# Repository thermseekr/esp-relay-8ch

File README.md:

# ESP-RELAY-8CH

ESP32 based board with 8x 24 VDC inputs and 8x 10A relay outputs.

This board is designed to be controlled by an Olimex ESP32-POE or ESP32-POE-ISO modules.

The dimensions are such that the board can be mounted on a PCB DIN rail holder from the Brazilian manufacturer Metaltex, check [here](https://www.metaltex.com.br/produtos/componentes/suportes/sp7-suporte-para-montagem-de-placa-de-circuito-impresso-em-trilho-din) for details.

## LICENSE

This project is licensed under the [Creative Commons BY-NC 4.0 License](https://creativecommons.org/licenses/by-nc/4.0/).
Commercial use is not permitted without prior written consent. See the [LICENSE.txt](LICENSE.txt) file for details.

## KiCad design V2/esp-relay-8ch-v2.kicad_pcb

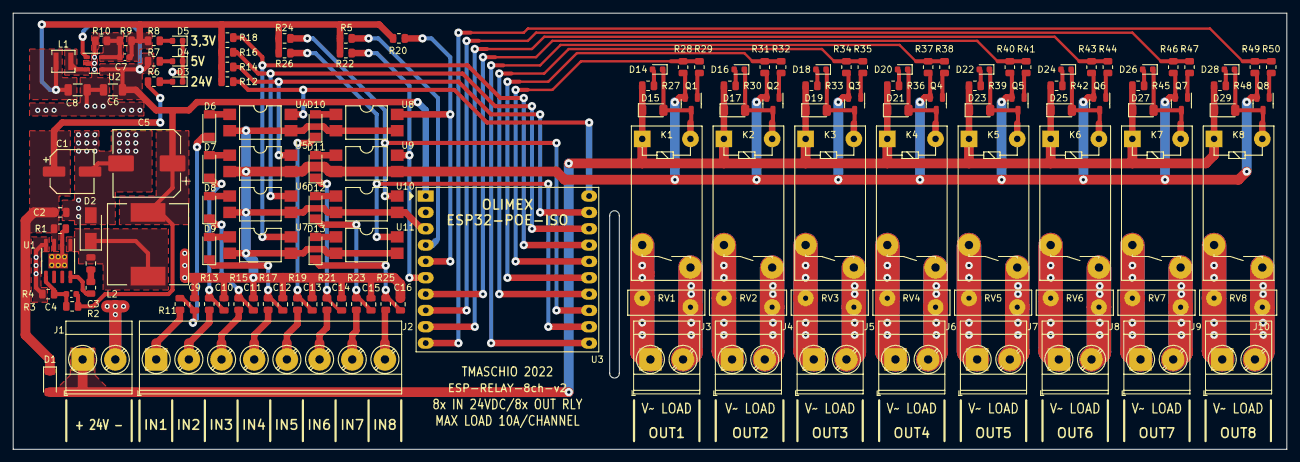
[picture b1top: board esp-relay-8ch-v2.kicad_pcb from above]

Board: 2 copper layers, 198.0 x 67.8 mm, 142 parts (0 on the bottom side), 96 nets.

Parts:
C1: 47uF/35V/6,3x5,4; CP_Elec_6.3x5.4
C2, C3: 0,1uF/50V/0805; C_0805_2012Metric
C4: 12pF/50V/0603; C_0603_1608Metric
C5: 470uF/16V/10x10; CP_Elec_10x10
C6, C8: 10uF/16V/1206; C_1206_3216Metric
C7: 22pF/50V/0603; C_0603_1608Metric
C9, C10, C11, C12, C13, C14, C15, C16: 33nF/50V/0805; C_0805_2012Metric
D1: SM4007PL/SOD-123; D_SOD-123
D2: SS510; D_SMA
D3, D4, D5, D14, D16, D18, D20, D22, D24, D26, D28: BLUE/0603; LED_0603_1608Metric
D6, D7, D8, D9, D10, D11, D12, D13: 9V1/500mW; D_MiniMELF
D15, D17, D19, D21, D23, D25, D27, D29: 1N4148/SOD-123; D_SOD-123
J1: +24VDC; TerminalBlock_Phoenix_MKDS-3-2-5.08_1x02_P5.08mm_Horizontal
J2: INPUTS; TerminalBlock_Phoenix_MKDS-3-8-5.08_1x08_P5.08mm_Horizontal
J3: OUT1; TerminalBlock_Phoenix_MKDS-3-2-5.08_1x02_P5.08mm_Horizontal
J4: OUT2; TerminalBlock_Phoenix_MKDS-3-2-5.08_1x02_P5.08mm_Horizontal
J5: OUT3; TerminalBlock_Phoenix_MKDS-3-2-5.08_1x02_P5.08mm_Horizontal
J6: OUT4; TerminalBlock_Phoenix_MKDS-3-2-5.08_1x02_P5.08mm_Horizontal
J7: OUT5; TerminalBlock_Phoenix_MKDS-3-2-5.08_1x02_P5.08mm_Horizontal
J8: OUT6; TerminalBlock_Phoenix_MKDS-3-2-5.08_1x02_P5.08mm_Horizontal
J9: OUT7; TerminalBlock_Phoenix_MKDS-3-2-5.08_1x02_P5.08mm_Horizontal
J10: OUT8; TerminalBlock_Phoenix_MKDS-3-2-5.08_1x02_P5.08mm_Horizontal
K1, K2, K3, K4, K5, K6, K7, K8: G5PZ-1A; Relay_SPST_Omron-G5PZ-1A
L1: 2,2uH 1,5A; L_3x3_H1.5
L2: 33uH 2,1A; L_12x12mm_H6mm
Q1, Q2, Q3, Q4, Q5, Q6, Q7, Q8: MMBT2222A/SOT-23-3; SOT-23
R1: 30mR/0,250W/0805; R_0805_2012Metric
R2: 5R1/0,125W/0805; R_0805_2012Metric
R3: 300k/0,125W/0805; R_0805_2012Metric
R4: 57,6k/0,125W/0805; R_0805_2012Metric
R5, R27, R30, R33, R36, R39, R42, R45, R48: 4k7/0,125W/0805; R_0805_2012Metric
R6: 5k6/0,125W/0805; R_0805_2012Metric
R7: 820R/0,125W/0805; R_0805_2012Metric
R8: 330R/0,125W/0805; R_0805_2012Metric
R9: 100k/0,125W/0805; R_0805_2012Metric
R10: 22,1k/0,125W/0805; R_0805_2012Metric
R11, R13, R15, R17, R19, R21, R23, R25: 1k2/0,125W/0805; R_0805_2012Metric
R12, R14, R16, R18, R20, R22, R24, R26: 3k3/0,125W/0805; R_0805_2012Metric
R28, R31, R34, R37, R40, R43, R46, R49: 10k/0,125W/0805; R_0805_2012Metric
R29, R32, R35, R38, R41, R44, R47, R50: 1k/0,125W/0805; R_0805_2012Metric
RV1, RV2, RV3, RV4, RV5, RV6, RV7, RV8: 250VAC; RV_Disc_D12mm_W3.9mm_P7.5mm
U1: TX4138; SOIC-8-1EP_3.9x4.9mm_P1.27mm_EP2.29x3mm_ThermalVias
U2: SY8089A1AAC; TSOT-23-5
U3: Olimex_ESP32-POE; Olimex_ESP32-POE_Pads
U4, U5, U6, U7, U8, U9, U10, U11: LTV-817S; SMDIP-4_W9.53mm

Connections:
+3.3V: C7.1, C8.1, L1.2, R5.1, R8.1, R9.1, R12.1, R14.1, R16.1, R18.1, R20.1, R22.1, R24.1, R26.1
+5V: C4.1, C5.1, C6.1, L2.2, R3.1, R7.1, U2.1 (EN), U2.4 (IN), U3.1 (5V)
+24V: D1.2 (A), D15.1 (K), D17.1 (K), D19.1 (K), D21.1 (K), D23.1 (K), D25.1 (K), D27.1 (K), D29.1 (K), J1.1, K1.1, K2.1, K3.1, K4.1, K5.1, K6.1, K7.1, K8.1, R27.1, R30.1, R33.1, R36.1, R39.1, R42.1, R45.1, R48.1
+VReg: C1.1, C2.1, D1.1 (K), R1.1, R6.1, U1.3 (VIN)
GNDREF: C1.2, C2.2, C5.2, C6.2, C8.2, C9.2, C10.2, C11.2, C12.2, C13.2, C14.2, C15.2, C16.2, D2.2 (A), D3.1 (K), D4.1 (K), D5.1 (K), J1.2, Q1.2 (E), Q2.2 (E), Q3.2 (E), Q4.2 (E), Q5.2 (E), Q6.2 (E), Q7.2 (E), Q8.2 (E), R4.2, R10.2, R28.2, R31.2, R34.2, R37.2, R40.2, R43.2, R46.2, R49.2, U1.4 (GND), U2.2 (GND), U3.3 (GND), U4.2, U4.3, U5.2, U5.3, U6.2, U6.3, U7.2, U7.3, U8.2, U8.3, U9.2, U9.3, U10.2, U10.3, U11.2, U11.3
IN1: R12.2, U3.20 (GPI39), U4.4
IN2: R14.2, U3.19 (GPI36\U1RXD), U5.4
IN3: R16.2, U3.18 (GPI35), U6.4
IN4: R18.2, U3.17 (GPI34\BUT1), U7.4
IN5: R20.2, U3.5 (GPIO0), U8.4
IN6: R22.2, U3.6 (GPIO1\U0TXD), U9.4
IN7: R24.2, U3.13 (GPIO15\HS2_CMD), U10.4
IN8: R26.2, U3.12 (GPIO14\HS2_CLK), U11.4
unnamed: C3.1, R2.1
unnamed: C3.2, D2.1 (K), L2.1, U1.1 (SW)
unnamed: C4.2, R3.2, R4.1, U1.5 (FB)
unnamed: C7.2, R9.2, R10.1, U2.5 (FB)
unnamed: C9.1, D6.1 (K), R11.1
unnamed: C10.1, D7.1 (K), R13.1
unnamed: C11.1, D8.1 (K), R15.1
unnamed: C12.1, D9.1 (K), R17.1
unnamed: C13.1, D10.1 (K), R19.1
unnamed: C14.1, D11.1 (K), R21.1
unnamed: C15.1, D12.1 (K), R23.1
unnamed: C16.1, D13.1 (K), R25.1
unnamed: D3.2 (A), R6.2
unnamed: D4.2 (A), R7.2
unnamed: D5.2 (A), R8.2
unnamed: D6.2 (A), U4.1
unnamed: D7.2 (A), U5.1
unnamed: D8.2 (A), U6.1
unnamed: D9.2 (A), U7.1
unnamed: D10.2 (A), U8.1
unnamed: D11.2 (A), U9.1
unnamed: D12.2 (A), U10.1
unnamed: D13.2 (A), U11.1
unnamed: D14.1 (K), D15.2 (A), K1.4, Q1.3 (C)
unnamed: D14.2 (A), R27.2
unnamed: D16.1 (K), D17.2 (A), K2.4, Q2.3 (C)
unnamed: D16.2 (A), R30.2
unnamed: D18.1 (K), D19.2 (A), K3.4, Q3.3 (C)
unnamed: D18.2 (A), R33.2
unnamed: D20.1 (K), D21.2 (A), K4.4, Q4.3 (C)
unnamed: D20.2 (A), R36.2
unnamed: D22.1 (K), D23.2 (A), K5.4, Q5.3 (C)
unnamed: D22.2 (A), R39.2
unnamed: D24.1 (K), D25.2 (A), K6.4, Q6.3 (C)
unnamed: D24.2 (A), R42.2
unnamed: D26.1 (K), D27.2 (A), K7.4, Q7.3 (C)
unnamed: D26.2 (A), R45.2
unnamed: D28.1 (K), D29.2 (A), K8.4, Q8.3 (C)
unnamed: D28.2 (A), R48.2
unnamed: J2.1, R11.2
unnamed: J2.2, R13.2
unnamed: J2.3, R15.2
unnamed: J2.4, R17.2
unnamed: J2.5, R19.2
unnamed: J2.6, R21.2
unnamed: J2.7, R23.2
unnamed: J2.8, R25.2
unnamed: J3.1, K1.2, RV1.1
unnamed: J3.2, K1.3, RV1.2
unnamed: J4.1, K2.2, RV2.1
unnamed: J4.2, K2.3, RV2.2
unnamed: J5.1, K3.2, RV3.1
unnamed: J5.2, K3.3, RV3.2
unnamed: J6.1, K4.2, RV4.1
unnamed: J6.2, K4.3, RV4.2
unnamed: J7.1, K5.2, RV5.1
unnamed: J7.2, K5.3, RV5.2
unnamed: J8.1, K6.2, RV6.1
unnamed: J8.2, K6.3, RV6.2
unnamed: J9.1, K7.2, RV7.1
unnamed: J9.2, K7.3, RV7.2
unnamed: J10.1, K8.2, RV8.1
unnamed: J10.2, K8.3, RV8.2
unnamed: L1.1, U2.3 (LX)
unnamed: Q1.1 (B), R29.1
unnamed: Q2.1 (B), R32.1
unnamed: Q3.1 (B), R35.1
unnamed: Q4.1 (B), R38.1
unnamed: Q5.1 (B), R41.1
unnamed: Q6.1 (B), R44.1
unnamed: Q7.1 (B), R47.1
unnamed: Q8.1 (B), R50.1
unnamed: R1.2, U1.2 (ILIM), U1.9 (ILIM)
unnamed: R2.2, U1.8 (BS)
unnamed: R5.2, U3.4 (ESP_EN)
OUT1: R28.1, R29.2, U3.16 (GPIO33)
OUT2: R31.1, R32.2, U3.15 (GPIO32)
OUT3: R34.1, R35.2, U3.14 (GPIO16\I2C-SCL)
OUT4: R37.1, R38.2, U3.11 (GPIO13\I2C-SDA)
OUT5: R40.1, R41.2, U3.7 (GPIO2\HS2\DATA0)
OUT6: R43.1, R44.2, U3.9 (GPIO4\U1TXD)
OUT7: R46.1, R47.2, U3.8 (GPIO3\U0RXD)
OUT8: R49.1, R50.2, U3.10 (GPIO5\SPI_CS)

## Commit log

2022-10-11 SCH and PCB updates
2022-10-11 SCH and PCB development
2022-10-13 Development
2022-10-14 SCH tweaks
2022-10-17 Removed V2
2022-10-19 PCB updates
2022-10-21 JLCPCB part update
2023-04-26 Can't remember!
2023-04-26 New images
2023-05-21 Update board images
2023-05-21 Update board image files.
2023-09-02 Design optimization
2023-09-06 Rename to lowercase
2023-09-22 New V2
2023-09-23 V2 design
2024-10-03 Update to Kicad 8
2025-06-30 Added license
